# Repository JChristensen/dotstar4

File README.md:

# DotStar4 Board
https://github.com/JChristensen/dotstar4  
README file  
Jack Christensen  
Dec-2020

## License
  
DotStar4 Board by Jack Christensen is licensed under a [Creative Commons Attribution-ShareAlike 4.0 International License](http://creativecommons.org/licenses/by-sa/4.0/).

## Overview
Just a simple board to hold four APA102C addressable RGB LEDs (a.k.a. DotStar, a.k.a. Lumenati). Multiple boards can be daisy chained, either end-to-end or from one end of the board.

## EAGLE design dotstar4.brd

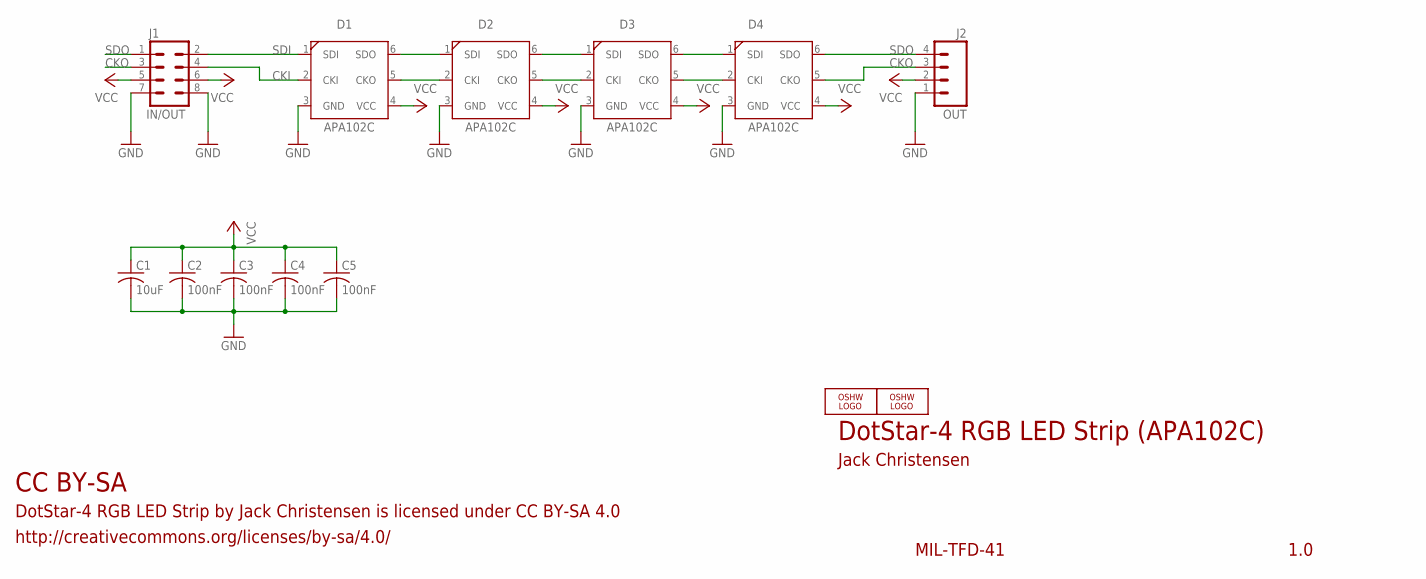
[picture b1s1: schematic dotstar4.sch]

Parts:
C1: 10uF; M0805
C2, C3, C4, C5: 100nF; M0805
D1, D2, D3, D4: APA102C; RGB5050
J1: IN/OUT; 2X4
J2: OUT; 1X04
LOGO1, LOGO2: OSHW_LOGO_8MILX0150-NT; OSHW_8X150_NOTEXT

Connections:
CKI: D1.2 (CKI), J1.4
CKO: D4.5 (CKO), J1.3, J2.3
GND: C1.2, C2.2, C3.2, C4.2, C5.2, D1.3 (GND), D2.3 (GND), D3.3 (GND), D4.3 (GND), J1.7, J1.8, J2.1
unnamed: D1.5 (CKO), D2.2 (CKI)
unnamed: D1.6 (SDO), D2.1 (SDI)
unnamed: D2.5 (CKO), D3.2 (CKI)
unnamed: D2.6 (SDO), D3.1 (SDI)
unnamed: D3.5 (CKO), D4.2 (CKI)
unnamed: D3.6 (SDO), D4.1 (SDI)
SDI: D1.1 (SDI), J1.2
SDO: D4.6 (SDO), J1.1, J2.4
VCC: C1.1, C2.1, C3.1, C4.1, C5.1, D1.4 (VCC), D2.4 (VCC), D3.4 (VCC), D4.4 (VCC), J1.5, J1.6, J2.2

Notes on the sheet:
DotStar-4 RGB LED Strip (APA102C)
Jack Christensen
MIL-TFD-41
1.0
CC BY-SA
DotStar-4 RGB LED Strip by Jack Christensen is licensed under CC BY-SA 4.0
http://creativecommons.org/licenses/by-sa/4.0/

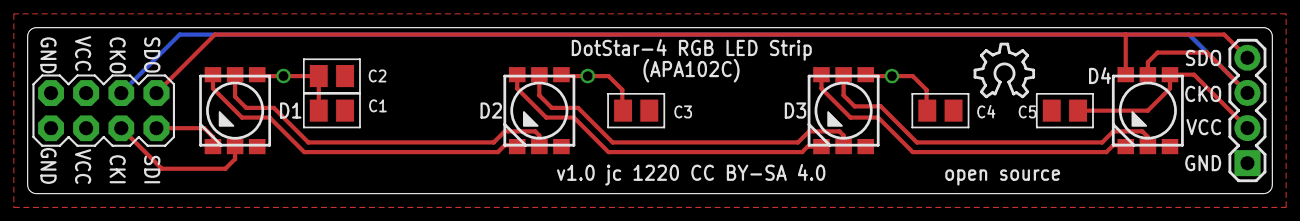
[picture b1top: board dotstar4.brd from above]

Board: 2 copper layers, 90.0 x 12.0 mm, 13 parts (1 on the bottom side), 12 nets.

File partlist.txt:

Partlist

Exported from dotstar4.sch at 12/14/20 6:06 PM

EAGLE Version 9.6.2 Copyright (c) 1988-2020 Autodesk, Inc.

Assembly variant: 

Part     Value          Device     Package  Library  Sheet

C1       10uF           C-USM0805  M0805    _jc      1
C2       100nF          C-USM0805  M0805    _jc      1
C3       100nF          C-USM0805  M0805    _jc      1
C4       100nF          C-USM0805  M0805    _jc      1
C5       100nF          C-USM0805  M0805    _jc      1
D1       APA102C        APA102C    RGB5050  _jc      1
D2       APA102C        APA102C    RGB5050  _jc      1
D3       APA102C        APA102C    RGB5050  _jc      1
D4       APA102C        APA102C    RGB5050  _jc      1
J1       IN/OUT         M04X2      2X4      SparkFun 1
J2       OUT            M04PTH     1X04     SparkFun 1

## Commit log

2020-12-14 Initial commit.
2020-12-14 Add .gitignore file.
2020-12-14 Replace erroneously named APA101C device with APA102C.
2021-01-16 Add images, partlist, license and readme files.

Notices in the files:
dotstar4.brd:
v1.0 jc 1220 CC BY-SA 4.0
parts and their libraries:
SparkFun: Licensing: CC v3.0 Share-Alike You are welcome to use this library for commercial purposes.
